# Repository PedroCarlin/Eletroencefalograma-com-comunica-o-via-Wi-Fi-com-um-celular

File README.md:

# Eletroencefalograma que adquiri e envia os dados via Wi-Fi para um celular
Projeto para construir um eletroencefalograma que faz a aquisição e envia o sinal para o celular, mostrando em um gráfico o sinal captado da eletroencefalografia.

Esse sistema é composto por duas placas, responsáveis por fazer a aquisição do sinal da eletroencefalografia (EEG), e por um ESP32 que é responsável por enviar os dados para o celular e armazenar a página web que irá montar o gráfico que representa o sinal do EEG.

Está disponível nesse repositório os arquivos necessários para construir as placas de aquisição e os códigos usados para programar o ESP32 e a página web.

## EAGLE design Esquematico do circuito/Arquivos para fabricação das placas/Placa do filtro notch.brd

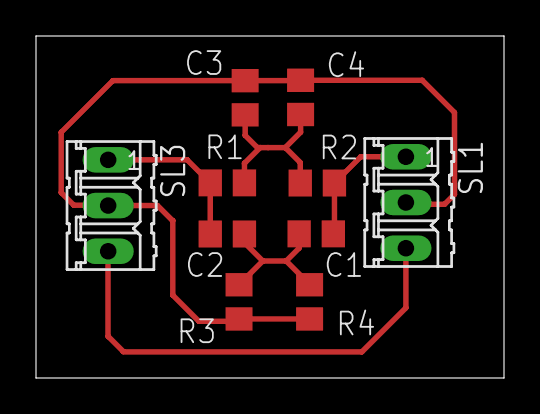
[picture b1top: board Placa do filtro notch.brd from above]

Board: 2 copper layers, 26.0 x 19.0 mm, 10 parts (0 on the bottom side), 6 nets.

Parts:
C1, C2, C3, C4: C0805
R1, R2, R3, R4: R0805
SL1, SL3: 03P

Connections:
unnamed: C1.2, C2.2, R3.2, R4.2
unnamed: C2.1, R1.1, SL3.1
unnamed: C3.1, C4.1, R3.1, R4.1, SL1.2, SL3.2
unnamed: C1.1, R2.2, SL1.1
unnamed: C3.2, C4.2, R1.2, R2.1
VCC: SL1.3, SL3.3

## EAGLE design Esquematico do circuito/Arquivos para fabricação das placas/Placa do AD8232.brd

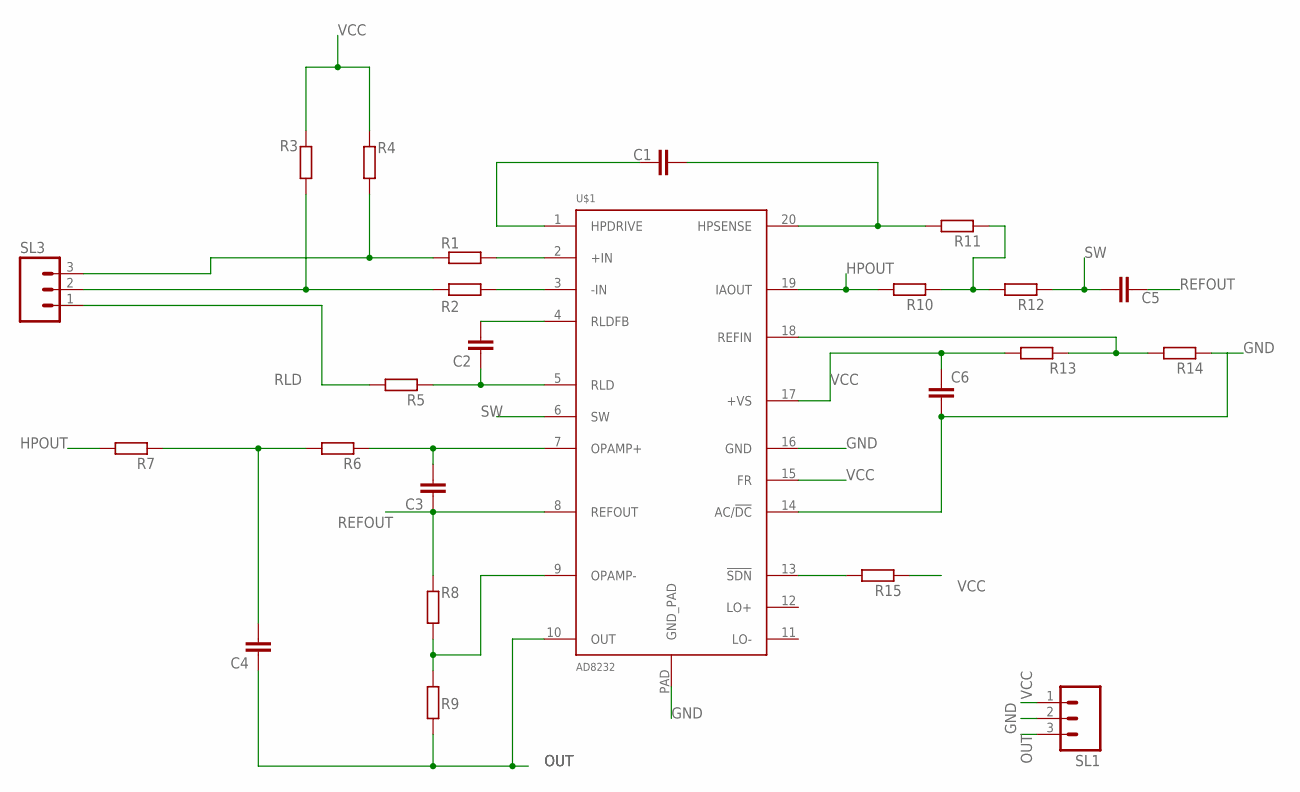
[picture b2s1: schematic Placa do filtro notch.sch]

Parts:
C1, C2, C3, C4, C5, C6: C-EUC0805; C0805
R1, R2, R3, R4, R5, R6, R7, R8, R9, R10, R11, R12, R13, R14, R15: R-EU_R0805; R0805
SL1, SL3: M03; 03P
U$1: AD8232; LFCSP_20

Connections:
GND: C6.2, R14.1, SL1.2, U$1.14 (AC/!DC), U$1.16 (GND), U$1.PAD (GND_PAD)
HPOUT: R7.2, R10.2, U$1.19 (IAOUT)
unnamed: C1.1, U$1.1 (HPDRIVE)
unnamed: C1.2, R11.2, U$1.20 (HPSENSE)
unnamed: R1.2, U$1.2 (+IN)
unnamed: R2.2, U$1.3 (-IN)
unnamed: R1.1, R4.1, SL3.3
unnamed: R2.1, R3.1, SL3.2
unnamed: C2.2, U$1.4 (RLDFB)
unnamed: C2.1, R5.1, U$1.5 (RLD)
unnamed: C3.2, R6.1, U$1.7 (OPAMP+)
unnamed: R13.1, R14.2, U$1.18 (REFIN)
unnamed: R8.2, R9.1, U$1.9 (OPAMP-)
unnamed: R10.1, R11.1, R12.2
unnamed: C4.2, R6.2, R7.1
unnamed: R15.2, U$1.13 (!SDN)
OUT: C4.1, R9.2, SL1.3, U$1.10 (OUT)
REFOUT: C3.1, C5.1, R8.1, U$1.8 (REFOUT)
RLD: R5.2, SL3.1
SW: C5.2, R12.1, U$1.6 (SW)
VCC: C6.1, R3.2, R4.2, R13.2, R15.1, SL1.1, U$1.15 (FR), U$1.17 (+VS)

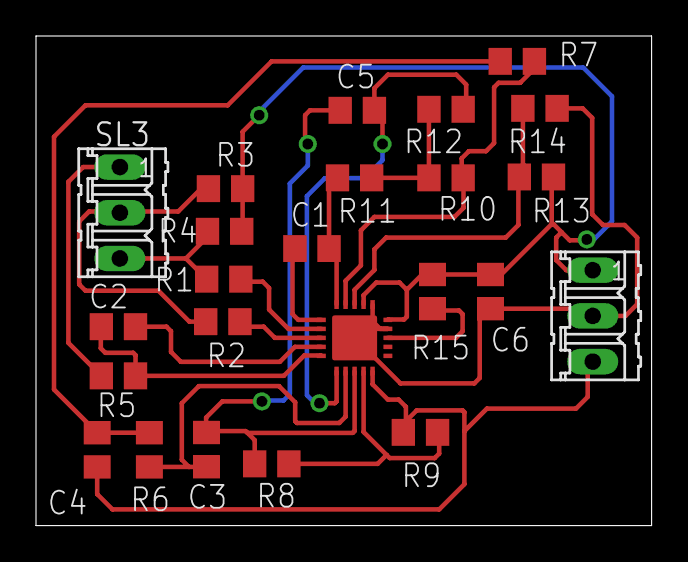
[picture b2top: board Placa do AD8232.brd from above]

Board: 2 copper layers, 34.2 x 27.2 mm, 24 parts (0 on the bottom side), 21 nets.
